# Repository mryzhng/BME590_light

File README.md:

# BME590_light
Let's make a light

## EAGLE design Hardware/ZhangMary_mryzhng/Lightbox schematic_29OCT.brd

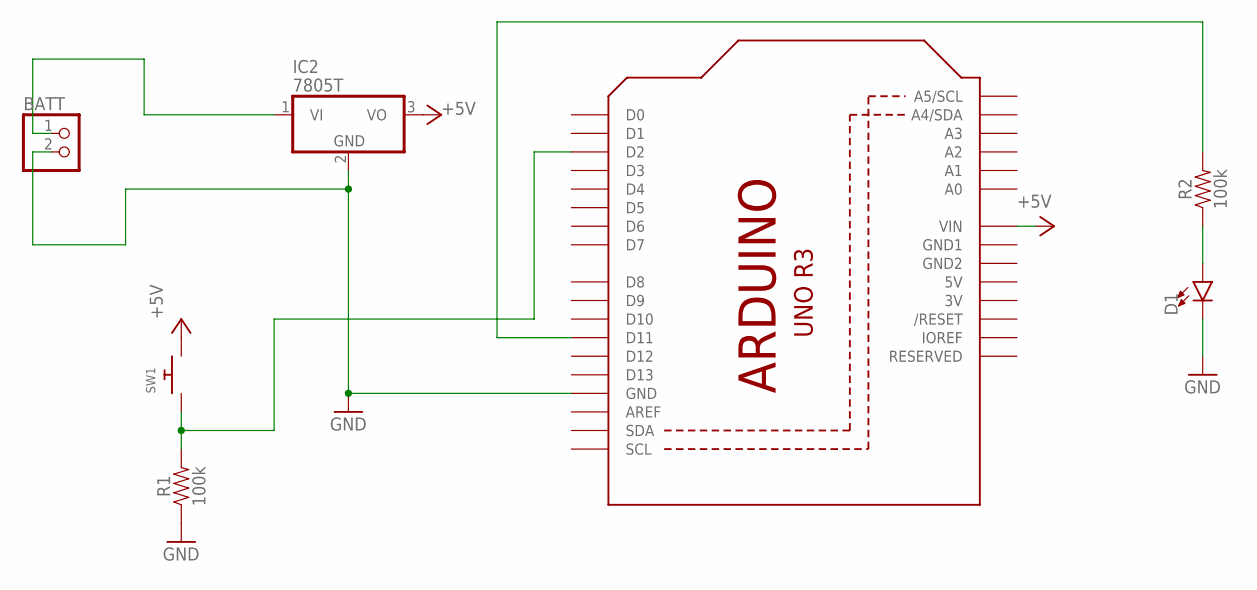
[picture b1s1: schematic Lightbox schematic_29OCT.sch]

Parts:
BATT: PINHD-1X2; 1X02
D1: LED3MM; LED_3MM
IC2: 7805T; TO220H
R1, R2: 100k; AXIAL-0.3
SW1: SWITCH_PUSHBUTTONSOFTTOUCHSMD_SJ; PUSHBUTTON_SMD_SJ
U1: ARDUINOR3-DIMENSION; ARDUINOR3

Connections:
3V: U1.3V
5V: U1.5V
+5V: IC2.3 (VO), SW1.P$2, U1.VIN
BATT: BATT.1, IC2.1 (VI)
GND: BATT.2, D1.K (C), IC2.2 (GND), R1.P$1 (1), U1.GND
GND1: U1.GND1
GND2: U1.GND2
unnamed: R1.P$2 (2), SW1.P$1, U1.D2
unnamed: R2.P$2 (2), U1.D11
unnamed: D1.A, R2.P$1 (1)

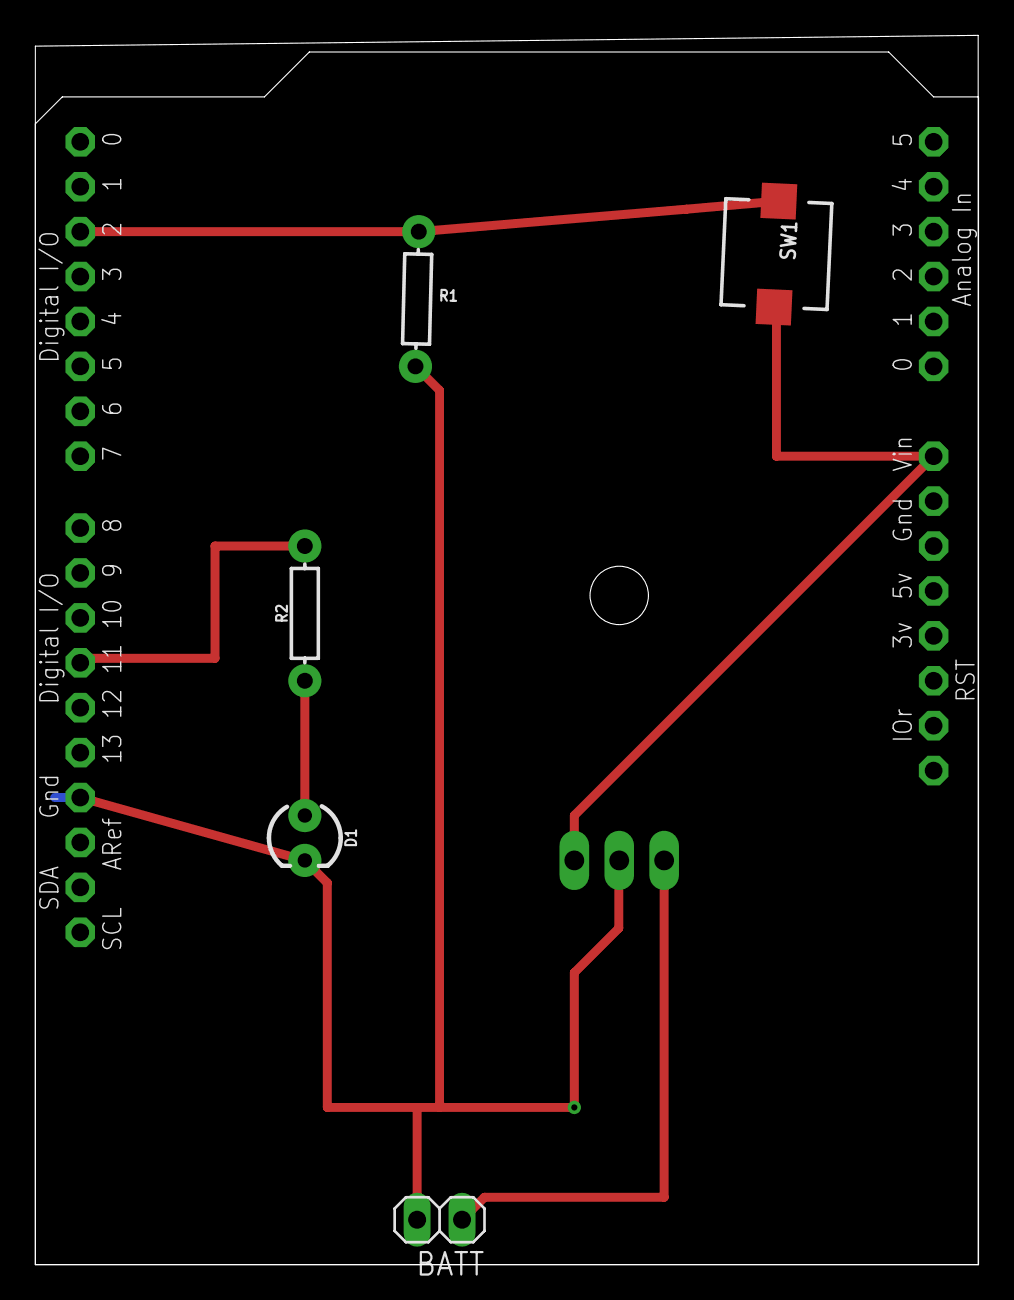
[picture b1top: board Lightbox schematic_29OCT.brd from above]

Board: 2 copper layers, 53.3 x 69.5 mm, 7 parts (1 on the bottom side), 6 nets.

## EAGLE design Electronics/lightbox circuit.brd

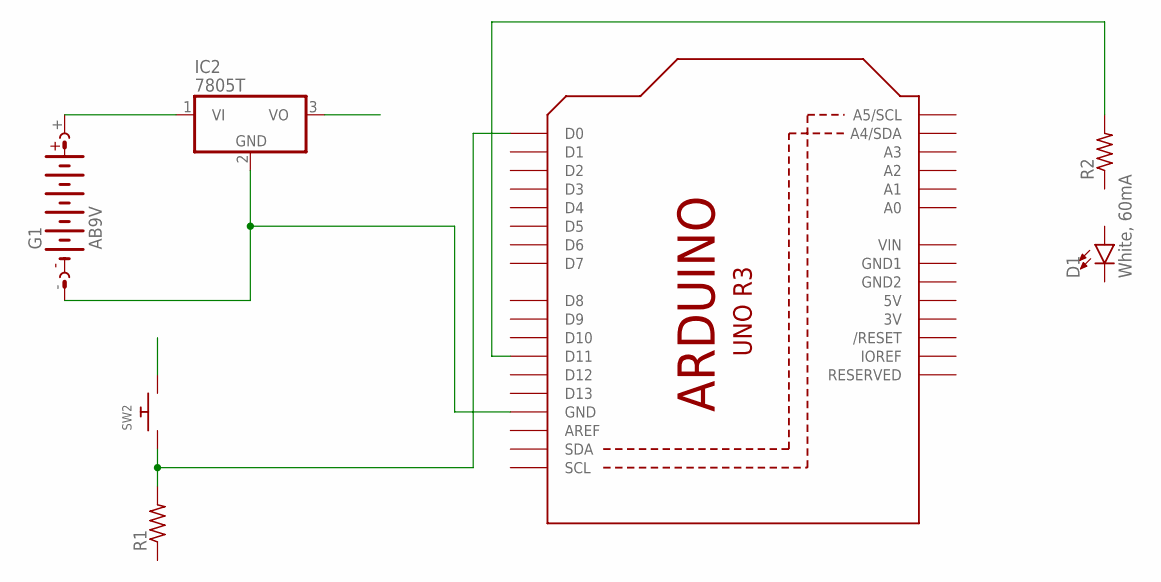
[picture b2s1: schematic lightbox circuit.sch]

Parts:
D1: White, 60mA; SUPER_BRIGHT_SMD_LED_3014
G1: AB9V
IC2: 7805T; TO220H
R1, R2: R-US_0414/15; 0414/15
SW2: SWITCH_PUSHBUTTONSOFTTOUCHSMD_SJ; PUSHBUTTON_SMD_SJ
U1: ARDUINOR3-DIMENSION; ARDUINOR3

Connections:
3V: U1.3V
5V: U1.5V
GND: G1.-, IC2.2 (GND), U1.GND
GND1: U1.GND1
GND2: U1.GND2
unnamed: R1.2, SW2.P$1, U1.D0
unnamed: G1.+, IC2.1 (VI)
unnamed: R2.2, U1.D11
VIN: U1.VIN

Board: 2 copper layers, 7 parts (0 on the bottom side), 4 nets, no tracks yet.

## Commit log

2018-11-01 v0.1.0
    milestone 03 ready for review
2018-11-01 v0.1.1
    updated milestone 03 ready for review
2018-11-01 v0.1.2
    updated milestone 03 ready for review
2018-11-08 v0.2.0
    milestone 04: updated board schematics
2018-11-08 v0.2.1
2018-11-13 v0.2.1
    updated lightbox arduino code
2018-11-13 create .txt file for code
2018-11-19 v0.3.0
    upload cad file
2018-11-19 schematic change
2018-11-19 add CAD+drawing file
2018-11-28 update PCB
2018-11-28 update MCAD
2018-11-28 update lightbox2
2018-11-28 updated light_box_2
2018-11-29 add revs of schematic/PCB iterated on in office
2018-12-03 PCB edt
2018-12-13 trial pictures

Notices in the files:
parts and their libraries:
SparkFun-LED: Licensing: Creative Commons ShareAlike 4.0 International - https://creativecommons.org/licenses/by-sa/4.0
